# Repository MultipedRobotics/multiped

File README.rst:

.. image:: https://raw.githubusercontent.com/walchko/quadruped/master/pics/spiderbot_dev.JPG
	:target: https://github.com/MomsFriendlyRobotCompany/quadruped
	:width: 75%

Quadruped
============================

.. image:: https://img.shields.io/pypi/v/quadruped.svg
	:target: https://github.com/MomsFriendlyRobotCompany/quadruped
.. image:: https://img.shields.io/pypi/l/quadruped.svg
	:target: https://github.com/MomsFriendlyRobotCompany/quadruped
.. image:: https://travis-ci.org/MomsFriendlyRobotCompany/quadruped.svg?branch=master
	:target: https://travis-ci.org/MomsFriendlyRobotCompany/quadruped

My robot software.

* `YouTube <https://www.youtube.com/watch?v=kH2hlxUfCNg>`_
* `Vimeo <https://player.vimeo.com/video/194676675>`_

Current State
----------------

.. image:: pics/spider.jpg
	:width: 75%

- Processor: Pi Zero W
- Language: python

ToDo:

- design/build boards instead of the jumpers connecting wires
- design the head structure to hold electronics and LCD

Documentation
-------------------

Install
-----------

pip
~~~~~

The recommended way to install this library is::

	pip install quadruped

Development
~~~~~~~~~~~~~

If you wish to develop and submit git-pulls, you can do::

	git clone https://github.com/MomsFriendlyRobotCompany/quadruped
	cd quadruped
	pip install -e .

Testing
~~~~~~~~~

Since I have both python2 and python3 installed, I need to test with both::

	python2 -m nose *.py
	python3 -m nose *.py

Layout
------------

Here is *sort* of the layout of the code:

- Robot(data)
  - Takes a dict of setup values: {'serialPort': /dev/something, 'write': 'bulk'}
		- Engine
		- Gait
- Gait:
	- Gait calculates the foot positions for 1 cycle of a movement
	- command() - plans all feet through 1 gait cycle (12 steps)
	- eachLeg(x,y,z)

- Engine:
	- Engine takes the output from Gait and calculates the servo joint positions
	  for each time stop and each leg in the cycle. It then sends the command to
	  move the servos at the end of the time step.
	- legs[4]
		- servos[3]
			- angle
			- setServoLimits()
			- bulkWrite()
			- syncWrite()
		- coxa, femur, tibia
		- fk() - forward kinematics
		- ik() - inverse kinematics
		- moveFoot(x,y,z) - for inverse kinematics
		- moveFootAngle(a,b,c) - for forward kinematics

The example quadruped (in the examples folder), takes a dictionary. Currently
it takes::

	data = {
		'serialPort': '/dev/tty.usbserial-AL034G2K',
		'write': 'bulk'
	}

If you don't pass it a serial port, then it falls back to a simulated serial
port which does nothing but is useful for testing.

Bulk Writing
--------------

Normally, you would send an individual command to each servo and get a response
back from it. That creates a lot of back an forth communications. Instead,
this uses a bulk write to send commands to all 12 servos at once with no reply.
This results in smoother motion and greatly reduced data transmission.

Building and Documentation
----------------------------

Details for how to build the robot and other information are in the ``docs`` folder
in the `git repo <https://github.com/MomsFriendlyRobotCompany/quadruped/tree/master/docs>`_

Tools
---------

This directory contains several tools for the robot:

- get_leg_angles.py: prints out the joint angles for all 4 legs

.. code-block:: bash

	$ ./get_leg_angles.py /dev/tty.usbserial-AL034G2K
	Opened /dev/tty.usbserial-AL034G2K @ 1000000

	Servos: 1 - 12
	All angles are in degrees
	         Leg 1 |         Leg 2 |         Leg 3 |         Leg 4 |
	   ID | Angle  |   ID | Angle  |   ID | Angle  |   ID | Angle  |
	-----------------------------------------------------------------
	    1 | 149.56 |    4 | 149.56 |    7 | 149.56 |   10 | 149.56
	    2 | 239.88 |    5 | 271.55 |    8 | 269.79 |   11 | 270.38
	    3 |  99.41 |    6 | 100.29 |    9 | 100.00 |   12 |  99.41
	-----------------------------------------------------------------

- get_leg_info.py: prints out servo information for all 12 servos on the robot

.. code-block:: bash

	$ ./get_leg_info.py /dev/tty.usbserial-AL034G2K
	Opened /dev/tty.usbserial-AL034G2K @ 1000000

	Servos: 1 - 12
	--------------------------------------------------
	Servo: 1  		HW Error: 0
	Position [deg]: 149.6  Load:   0.0% CCW
	Voltage [V]  7.0     Temperature [F]:  80.6
	--------------------------------------------------
	Servo: 2  		HW Error: 0
	Position [deg]: 239.6  Load:   0.0% CCW
	Voltage [V]  7.2     Temperature [F]:  80.6
	--------------------------------------------------
	Servo: 3  		HW Error: 0
	Position [deg]:  99.4  Load:   0.0% CCW
	Voltage [V]  7.2     Temperature [F]:  82.4
	--------------------------------------------------
	Servo: 4  		HW Error: 0
	Position [deg]: 149.6  Load:   0.0% CCW
	Voltage [V]  7.3     Temperature [F]:  80.6
	--------------------------------------------------
	Servo: 5  		HW Error: 0
	Position [deg]: 271.6  Load:   0.0% CCW
	Voltage [V]  7.2     Temperature [F]:  80.6
	--------------------------------------------------
	Servo: 6  		HW Error: 0
	Position [deg]: 100.3  Load:   0.0% CCW
	Voltage [V]  7.4     Temperature [F]:  82.4
	--------------------------------------------------
	Servo: 7  		HW Error: 0
	Position [deg]: 149.6  Load:   0.0% CCW
	Voltage [V]  7.2     Temperature [F]:  80.6
	--------------------------------------------------
	Servo: 8  		HW Error: 0
	Position [deg]: 269.8  Load:   0.0% CCW
	Voltage [V]  7.1     Temperature [F]:  78.8
	--------------------------------------------------
	Servo: 9  		HW Error: 0
	Position [deg]:  99.4  Load:   0.8% CCW
	Voltage [V]  7.2     Temperature [F]:  82.4
	--------------------------------------------------
	Servo: 10  		HW Error: 0
	Position [deg]: 149.9  Load:   0.0% CCW
	Voltage [V]  7.1     Temperature [F]:  80.6
	--------------------------------------------------
	Servo: 11  		HW Error: 0
	Position [deg]: 270.1  Load:   0.0% CCW
	Voltage [V]  7.2     Temperature [F]:  80.6
	--------------------------------------------------
	Servo: 12  		HW Error: 0
	Position [deg]:  99.4  Load:   0.0% CCW
	Voltage [V]  7.1     Temperature [F]:  84.2
	--------------------------------------------------

Change Log
-------------

============ ======= ============================
2017-12-25   0.5.0   Clean up and reorg, removed unnecessary libraries
2017-06-07   0.4.1   broke out into package and published to PyPi
2016-08-10   0.0.1   init
============ ======= ============================

MIT License
---------------

**Copyright (c) 2016 Kevin J. Walchko**

Permission is hereby granted, free of charge, to any person obtaining a copy of
this software and associated documentation files (the "Software"), to deal in
the Software without restriction, including without limitation the rights to
use, copy, modify, merge, publish, distribute, sublicense, and/or sell copies
of the Software, and to permit persons to whom the Software is furnished to do
so, subject to the following conditions:

The above copyright notice and this permission notice shall be included in all
copies or substantial portions of the Software.

THE SOFTWARE IS PROVIDED "AS IS", WITHOUT WARRANTY OF ANY KIND, EXPRESS OR
IMPLIED, INCLUDING BUT NOT LIMITED TO THE WARRANTIES OF MERCHANTABILITY, FITNESS
FOR A PARTICULAR PURPOSE AND NONINFRINGEMENT. IN NO EVENT SHALL THE AUTHORS OR
COPYRIGHT HOLDERS BE LIABLE FOR ANY CLAIM, DAMAGES OR OTHER LIABILITY, WHETHER
IN AN ACTION OF CONTRACT, TORT OR OTHERWISE, ARISING FROM, OUT OF OR IN
CONNECTION WITH THE SOFTWARE OR THE USE OR OTHER DEALINGS IN THE SOFTWARE.

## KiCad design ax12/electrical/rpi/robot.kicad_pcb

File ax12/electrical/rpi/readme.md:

# RPi Adaptor Board

This ties the RPi to sensors and actuators.

## Schematic

[pdf schematic](rpi.pdf)

## Board

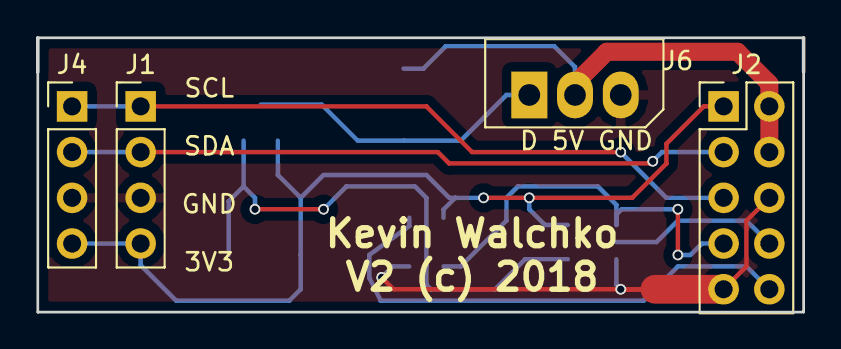
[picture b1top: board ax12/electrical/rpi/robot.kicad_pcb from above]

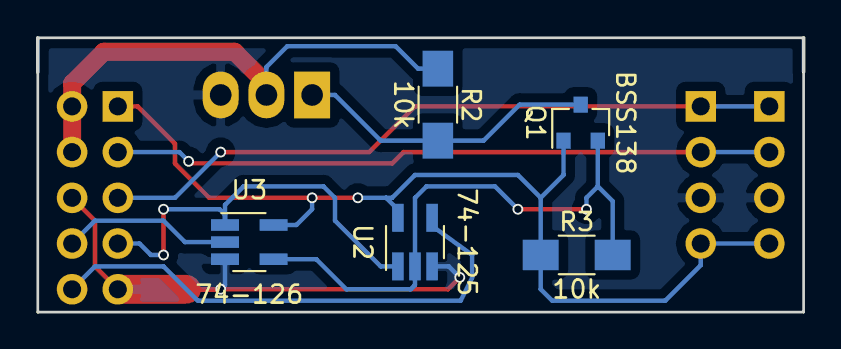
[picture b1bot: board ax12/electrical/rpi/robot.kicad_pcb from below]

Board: 2 copper layers, 42.5 x 15.2 mm, 9 parts (5 on the bottom side), 10 nets.

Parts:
J1, J4: i2c; Pin_Header_Straight_1x04_Pitch2.54mm
J2: Pi Header; Pin_Header_Straight_2x05_Pitch2.54mm
J6: Power/Data Input; Molex_SPOX-5267_22-03-5035_03x2.54mm_Straight
Q1: BSS138; SOT-23
R2, R3: 10k; R_1206_HandSoldering
U2: 74-125; SOT-23-5_HandSoldering
U3: 74-126; SOT-23-5_HandSoldering

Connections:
+3V3: J1.4, J2.1, J4.4, Q1.1, R3.1, U2.5, U3.5
+5V: J2.2, J2.4, J6.2, R2.1
DATA: J6.1, Q1.3, R2.2
DTR: J2.7, U2.1, U3.1
GND: J1.3, J2.6, J2.9, J4.3, J6.3, U2.3, U3.3
unnamed: Q1.2, R3.2, U2.2, U3.4
RXI: J2.10, U2.4
SCL: J1.1, J2.5, J4.1
SDA: J1.2, J2.3, J4.2
TXO: J2.8, U3.2

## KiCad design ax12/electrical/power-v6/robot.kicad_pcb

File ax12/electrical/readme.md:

# Electrical

## Raspberry Pi

Adaptor board to connect the RPi to sensors/actuators

## Power

Power distribution board

### Pololu 12V Buck Regulator

# Bill of Materials (BoM)

| Part | Qnty | Each | Cost |
|---|---|---|---|
|  |  |  |  |

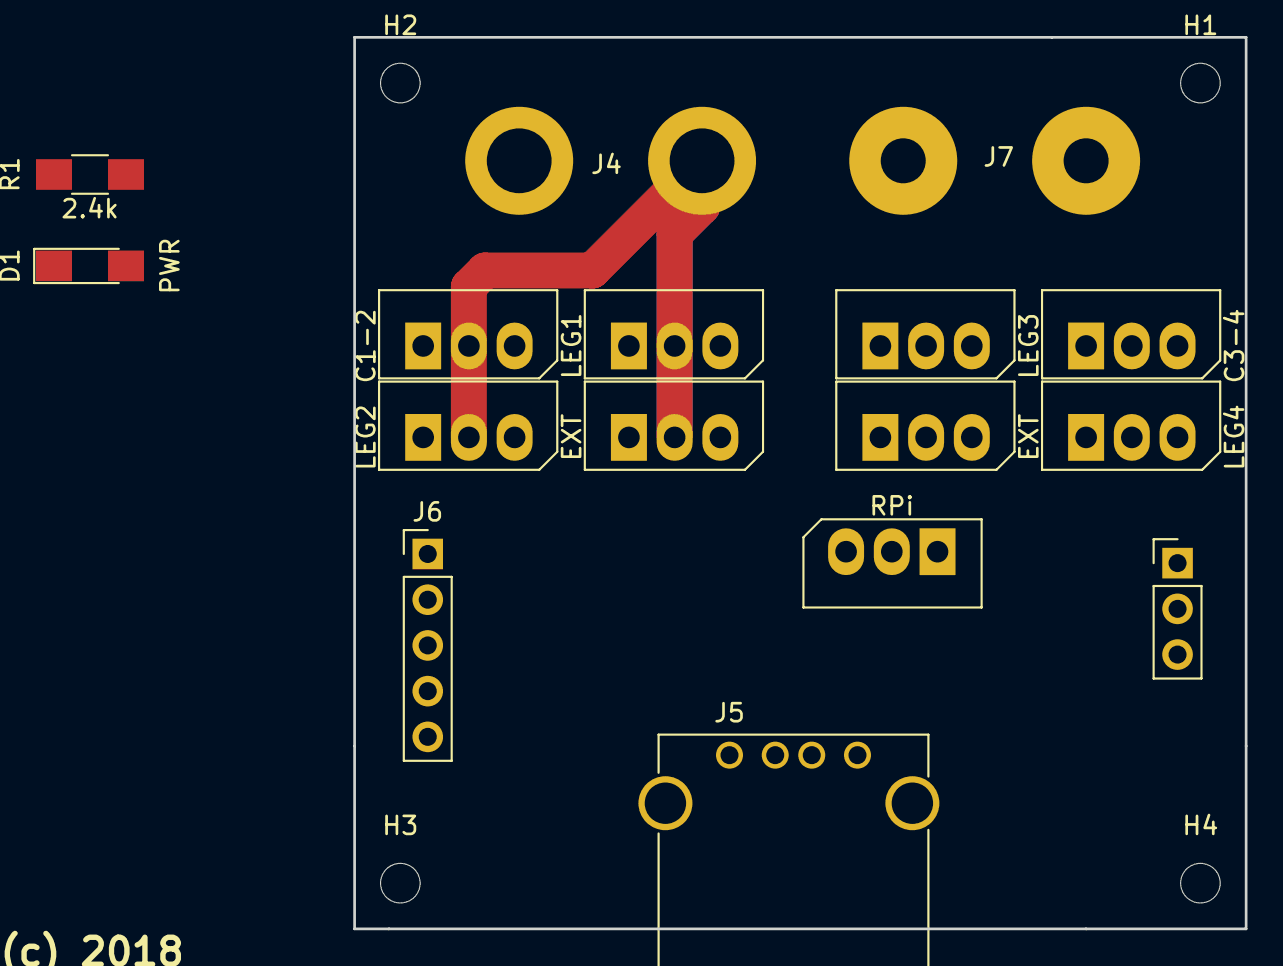
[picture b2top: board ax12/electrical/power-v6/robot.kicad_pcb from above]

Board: 2 copper layers, 49.5 x 49.5 mm, 20 parts (0 on the bottom side), 6 nets.

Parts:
D1: PWR; LED_1206_HandSoldering
H1, H2, H3, H4: MountingHole; MountingHole_2.2mm_M2
J1: C1-2; Molex_SPOX-5267_22-03-5035_03x2.54mm_Straight
J2: RPi; Molex_SPOX-5267_22-03-5035_03x2.54mm_Straight
J3: Data; Pin_Header_Straight_1x03_Pitch2.54mm
J4: Leg1-2; WireConnection_2.50mmDrill_LargePad
J5: USB_A
J6: 5V Pwr; Pin_Header_Straight_1x05_Pitch2.54mm
J7: Leg3-4; WireConnection_2.50mmDrill_LargePad
J8: LEG1; Molex_SPOX-5267_22-03-5035_03x2.54mm_Straight
J10: LEG2; Molex_SPOX-5267_22-03-5035_03x2.54mm_Straight
J11, J13: EXT; Molex_SPOX-5267_22-03-5035_03x2.54mm_Straight
J12: LEG4; Molex_SPOX-5267_22-03-5035_03x2.54mm_Straight
J14: C3-4; Molex_SPOX-5267_22-03-5035_03x2.54mm_Straight
J15: LEG3; Molex_SPOX-5267_22-03-5035_03x2.54mm_Straight
R1: 2.4k; R_1206_HandSoldering

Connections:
+5V: J2.2, J5.1, J6.5
DATA: J1.1, J2.1, J3.1, J8.1, J10.1, J11.1, J12.1, J13.1, J14.1, J15.1
GND: J1.3, J2.3, J3.3, J4.1, J5.4, J5.5, J6.3, J6.4, J7.1, J8.3, J10.3, J11.3, J12.3, J13.3, J14.3, J15.3, R1.2
unnamed: D1.1, R1.1
unnamed: D1.2, J1.2, J4.2, J6.2, J8.2, J10.2, J11.2
unnamed: J3.2, J7.2, J12.2, J13.2, J14.2, J15.2

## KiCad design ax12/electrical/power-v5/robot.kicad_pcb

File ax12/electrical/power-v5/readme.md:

# Power Distribution Board

## Schematic

[pdf schematic](rpi.pdf)

## Board

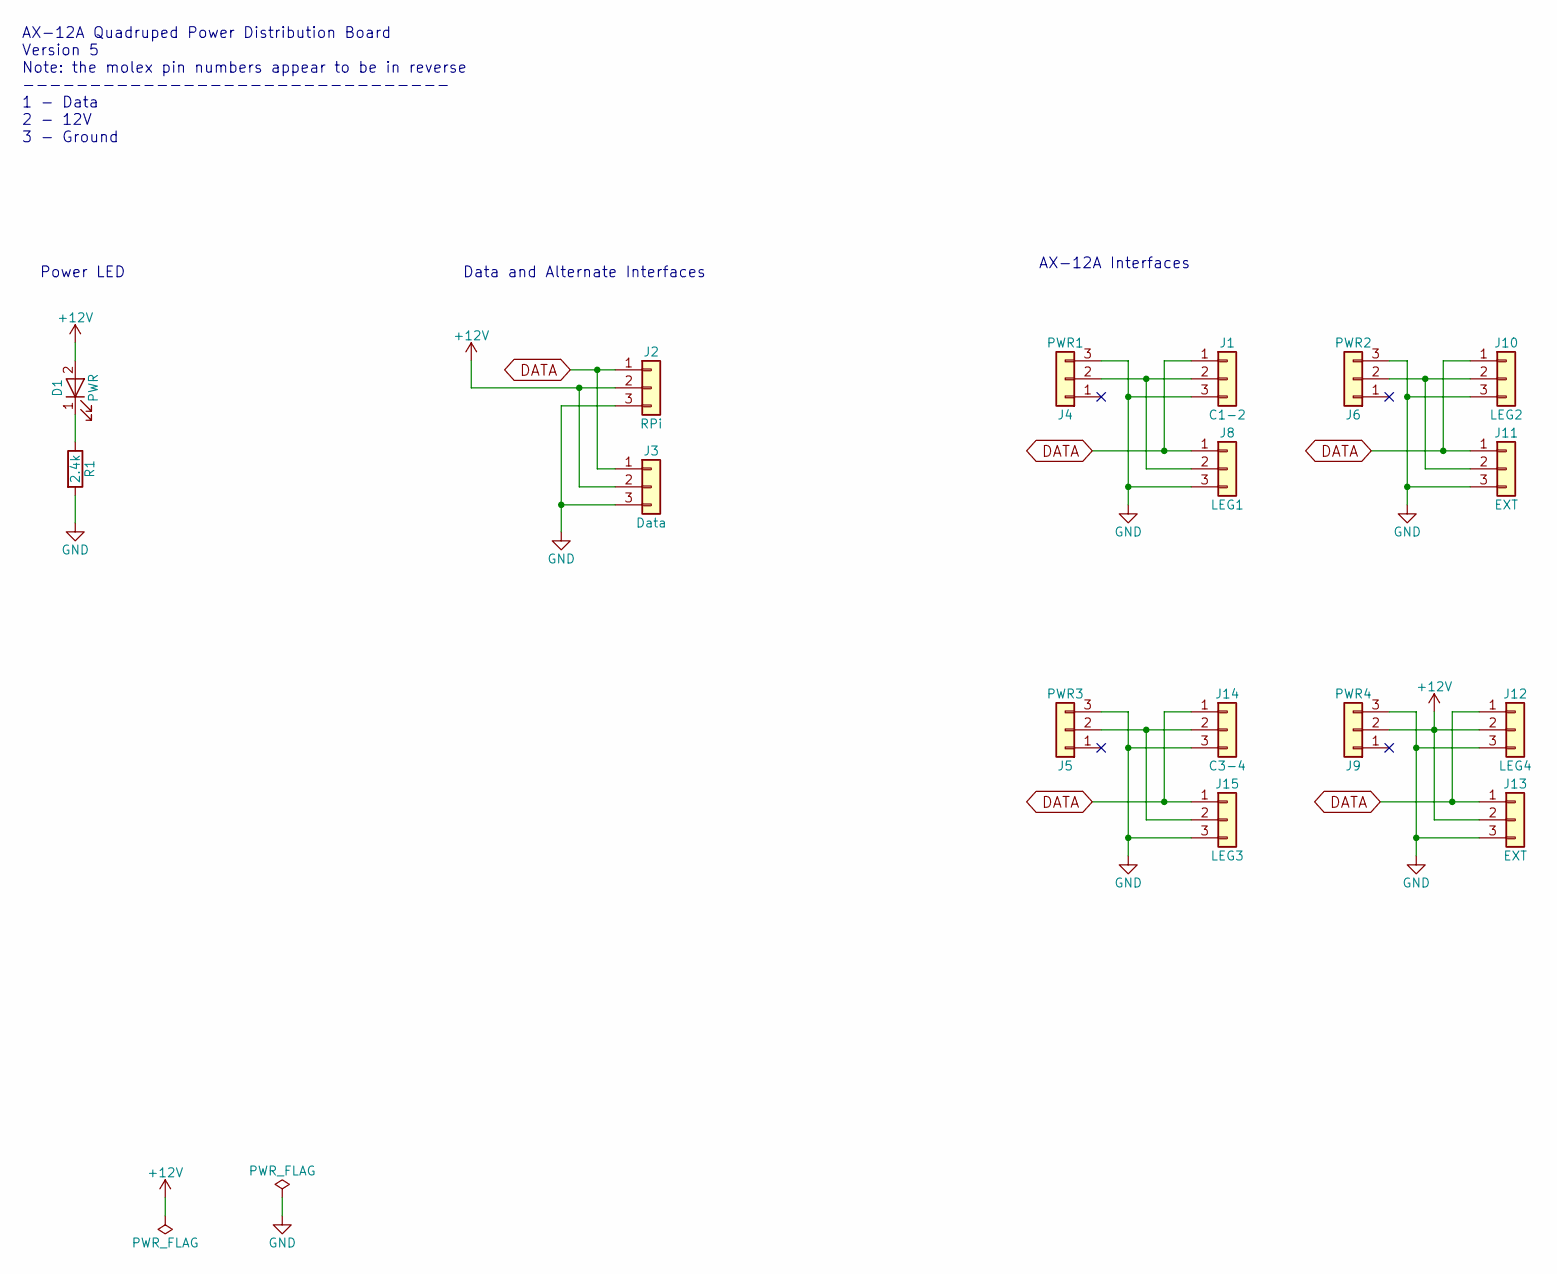
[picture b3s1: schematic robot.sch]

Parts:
D1: PWR; LED_1206_HandSoldering
J1: C1-2; Molex_SPOX-5267_22-03-5035_03x2.54mm_Straight
J2: RPi; Molex_SPOX-5267_22-03-5035_03x2.54mm_Straight
J3: Data; Pin_Header_Straight_1x03_Pitch2.54mm
J4: PWR1; Molex_SPOX-5267_22-03-5035_03x2.54mm_Straight
J5: PWR3; Molex_SPOX-5267_22-03-5035_03x2.54mm_Straight
J6: PWR2; Molex_SPOX-5267_22-03-5035_03x2.54mm_Straight
J8: LEG1; Molex_SPOX-5267_22-03-5035_03x2.54mm_Straight
J9: PWR4; Molex_SPOX-5267_22-03-5035_03x2.54mm_Straight
J10: LEG2; Molex_SPOX-5267_22-03-5035_03x2.54mm_Straight
J11, J13: EXT; Molex_SPOX-5267_22-03-5035_03x2.54mm_Straight
J12: LEG4; Molex_SPOX-5267_22-03-5035_03x2.54mm_Straight
J14: C3-4; Molex_SPOX-5267_22-03-5035_03x2.54mm_Straight
J15: LEG3; Molex_SPOX-5267_22-03-5035_03x2.54mm_Straight
R1: 2.4k; R_1206_HandSoldering

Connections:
+12V: D1.2 (A), J2.2, J3.2, J9.2, J12.2, J13.2
DATA: J1.1, J2.1, J3.1, J8.1, J10.1, J11.1, J12.1, J13.1, J14.1, J15.1
GND: J1.3, J2.3, J3.3, J4.3, J5.3, J6.3, J8.3, J9.3, J10.3, J11.3, J12.3, J13.3, J14.3, J15.3, R1.2
unnamed: D1.1 (K), R1.1
unnamed: J1.2, J4.2, J8.2
unnamed: J6.2, J10.2, J11.2
unnamed: J5.2, J14.2, J15.2

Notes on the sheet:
AX-12A Quadruped Power Distribution Board Version 5 Note: the molex pin numbers appear to be in reverse -------------------------------- 1 - Data 2 - 12V 3 - Ground
Power LED
AX-12A Interfaces
Data and Alternate Interfaces

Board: 2 copper layers, 16 parts (0 on the bottom side), 7 nets, no tracks yet.

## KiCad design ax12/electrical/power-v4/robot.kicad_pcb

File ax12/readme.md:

# AX-12A Quadruped

Nature loves animals/insects with legs. Even birds have legs! Legs allow for easier
navigation across rough terrain. The more legs you have, the more redundant and
robust you are. If you are a centipede and you break a few legs, no big deal.
However, if you are a human and break one leg, then walking (forget running)
becomes extremely difficult.

In robotics you see many different types of walking robots. Common ones are:
2 legs, four legs, and 6 legs. There are advantages and disadvantages for each
of these types of robots.

- 2 legs
    - balancing and shifting the body's center of mass is critical to the
robot not falling over
    - the 2 legs are generally need to be more powerful to lift the body mass
- 4 legs:
    - there is an inherent stability with this configuration. You only need 3
    legs (tripod) to keep the robot standing, leaving one leg to move freely
    as needed
    - each of the legs can be weaker (which also translates into cost $$$) than
    its 2 legged counter part, but you still have more of them, so it is probably
    still more expensive
    - However, there is still a lot of motors, data lines, coordination complexity
    than if you only had 2 legs
- 6 legs:
    - having more than 4 legs contains all of the same advantages/disadvantages
    of 4 legs
    - you also have more redundancy, essentially able to loose 2 legs and keep
    walking
    - there are also more types of gaits available to you, which is a fancy word
    for how you control your leg moves when walking, trotting, running, etc

**Still under development**

- [Mechanical Hardware](mechanical/)
- [Electrical Hardware](electrical/)

MIT License
-----------

**Copyright (c) 2018 Kevin J. Walchko**

Permission is hereby granted, free of charge, to any person obtaining a
copy of this software and associated documentation files (the
"Software"), to deal in the Software without restriction, including
without limitation the rights to use, copy, modify, merge, publish,
distribute, sublicense, and/or sell copies of the Software, and to
permit persons to whom the Software is furnished to do so, subject to
the following conditions:

The above copyright notice and this permission notice shall be included
in all copies or substantial portions of the Software.

THE SOFTWARE IS PROVIDED "AS IS", WITHOUT WARRANTY OF ANY KIND,
EXPRESS OR IMPLIED, INCLUDING BUT NOT LIMITED TO THE WARRANTIES OF
MERCHANTABILITY, FITNESS FOR A PARTICULAR PURPOSE AND NONINFRINGEMENT.
IN NO EVENT SHALL THE AUTHORS OR COPYRIGHT HOLDERS BE LIABLE FOR ANY
CLAIM, DAMAGES OR OTHER LIABILITY, WHETHER IN AN ACTION OF CONTRACT,
TORT OR OTHERWISE, ARISING FROM, OUT OF OR IN CONNECTION WITH THE
SOFTWARE OR THE USE OR OTHER DEALINGS IN THE SOFTWARE.

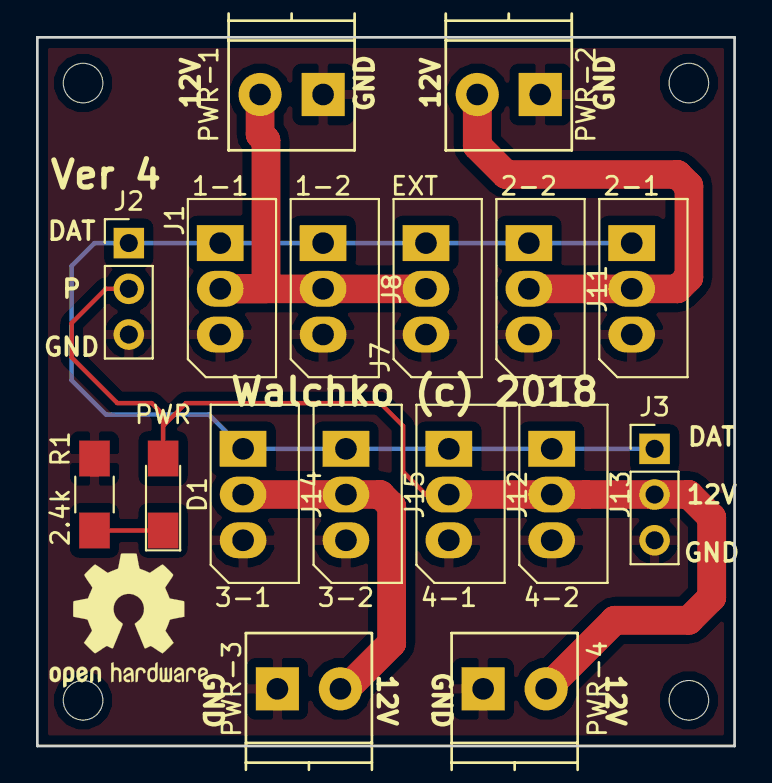
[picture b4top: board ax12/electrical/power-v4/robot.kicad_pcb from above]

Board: 2 copper layers, 38.7 x 39.4 mm, 17 parts (0 on the bottom side), 7 nets.

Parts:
D1: PWR; LED_1206_HandSoldering
J1: 1-1; Molex_SPOX-5267_22-03-5035_03x2.54mm_Straight
J2, J3: Data; Pin_Header_Straight_1x03_Pitch2.54mm
J4: PWR-4; TerminalBlock_Phoenix_PT-3.5mm_2pol
J5: PWR-3; TerminalBlock_Phoenix_PT-3.5mm_2pol
J6: PWR-1; TerminalBlock_Phoenix_PT-3.5mm_2pol
J7: EXT; Molex_SPOX-5267_22-03-5035_03x2.54mm_Straight
J8: 1-2; Molex_SPOX-5267_22-03-5035_03x2.54mm_Straight
J9: PWR-2; TerminalBlock_Phoenix_PT-3.5mm_2pol
J10: 2-1; Molex_SPOX-5267_22-03-5035_03x2.54mm_Straight
J11: 2-2; Molex_SPOX-5267_22-03-5035_03x2.54mm_Straight
J12: 4-1; Molex_SPOX-5267_22-03-5035_03x2.54mm_Straight
J13: 4-2; Molex_SPOX-5267_22-03-5035_03x2.54mm_Straight
J14: 3-1; Molex_SPOX-5267_22-03-5035_03x2.54mm_Straight
J15: 3-2; Molex_SPOX-5267_22-03-5035_03x2.54mm_Straight
R1: 2.4k; R_1206_HandSoldering

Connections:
+12V: D1.2, J2.2, J3.2, J4.2, J12.2, J13.2
DATA: J1.1, J2.1, J3.1, J7.1, J8.1, J10.1, J11.1, J12.1, J13.1, J14.1, J15.1
GND: J1.3, J2.3, J3.3, J4.1, J5.1, J6.1, J7.3, J8.3, J9.1, J10.3, J11.3, J12.3, J13.3, J14.3, J15.3, R1.2
unnamed: D1.1, R1.1
unnamed: J1.2, J6.2, J7.2, J8.2
unnamed: J9.2, J10.2, J11.2
unnamed: J5.2, J14.2, J15.2

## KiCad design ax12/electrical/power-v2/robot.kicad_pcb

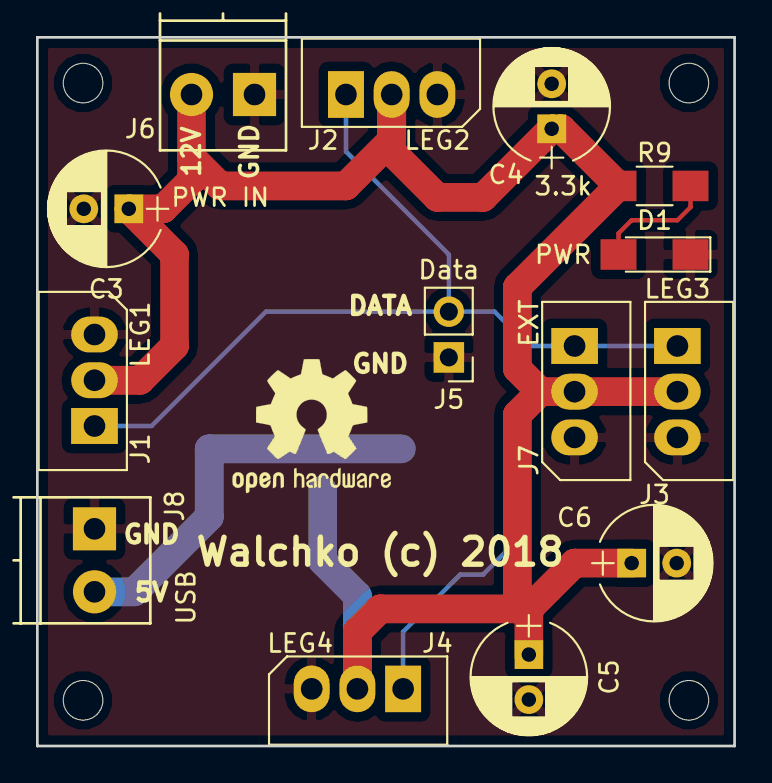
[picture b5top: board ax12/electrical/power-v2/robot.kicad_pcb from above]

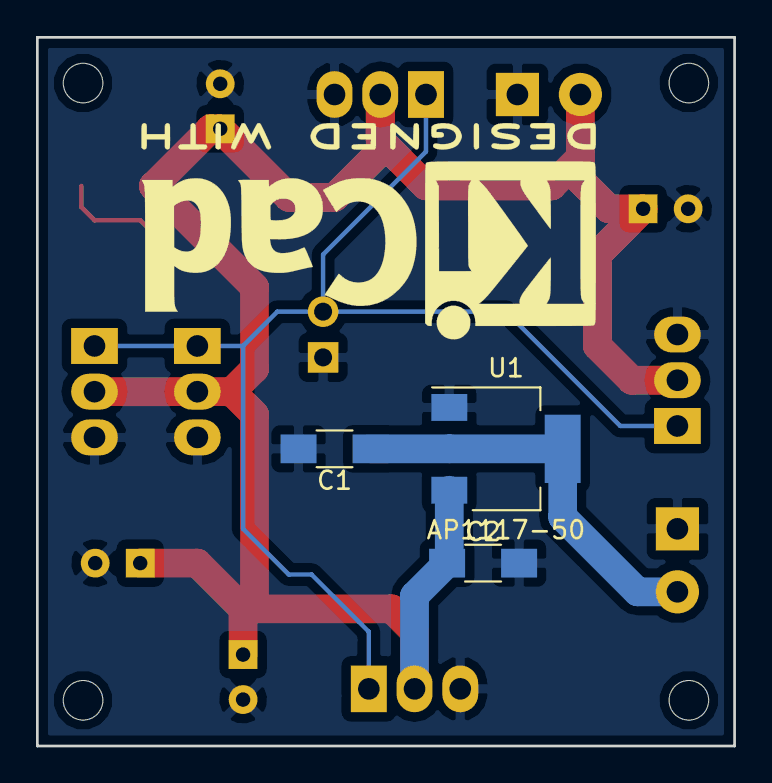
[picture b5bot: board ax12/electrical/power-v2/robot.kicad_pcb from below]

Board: 2 copper layers, 38.7 x 39.4 mm, 17 parts (3 on the bottom side), 5 nets.

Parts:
C1, C2: C; C_1206_HandSoldering
C3, C4, C5, C6: .1; CP_Radial_D6.3mm_P2.50mm
D1: PWR; LED_1206_HandSoldering
J1: LEG1; Molex_SPOX-5267_22-03-5035_03x2.54mm_Straight
J2: LEG2; Molex_SPOX-5267_22-03-5035_03x2.54mm_Straight
J3: LEG3; Molex_SPOX-5267_22-03-5035_03x2.54mm_Straight
J4: LEG4; Molex_SPOX-5267_22-03-5035_03x2.54mm_Straight
J5: Data; Pin_Header_Straight_1x02_Pitch2.54mm
J6: PWR IN; TerminalBlock_Phoenix_PT-3.5mm_2pol
J7: EXT; Molex_SPOX-5267_22-03-5035_03x2.54mm_Straight
J8: USB; TerminalBlock_Phoenix_PT-3.5mm_2pol
R9: 3.3k; R_1206_HandSoldering
U1: AP1117-50; SOT-223-3_TabPin2

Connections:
+5V: C1.1, J8.2, U1.2
+12V: C2.1, C3.1, C4.1, C5.1, C6.1, J1.2, J2.2, J3.2, J4.2, J6.2, J7.2, R9.1, U1.3
DATA: J1.1, J2.1, J3.1, J4.1, J5.2, J7.1
GND: C1.2, C2.2, C3.2, C4.2, C5.2, C6.2, D1.1, J1.3, J2.3, J3.3, J4.3, J5.1, J6.1, J7.3, J8.1, U1.1
unnamed: D1.2, R9.2

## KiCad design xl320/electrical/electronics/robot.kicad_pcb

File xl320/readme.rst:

.. image:: https://raw.githubusercontent.com/walchko/quadruped/master/pics/spiderbot_dev.JPG
	:target: https://github.com/MomsFriendlyRobotCompany/quadruped
	:width: 75%

XL-320 Quadruped
============================

My robot software.

* `YouTube <https://www.youtube.com/watch?v=kH2hlxUfCNg>`_
* `Vimeo <https://player.vimeo.com/video/194676675>`_

Documentation
-------------------

Install
-----------

pip
~~~~~

The recommended way to install this library is::

	pip install quadruped

Development
~~~~~~~~~~~~~

If you wish to develop and submit git-pulls, you can do::

	git clone https://github.com/MomsFriendlyRobotCompany/quadruped
	cd quadruped
	pip install -e .

Testing
~~~~~~~~~

Since I have both python2 and python3 installed, I need to test with both::

	python2 -m nose *.py
	python3 -m nose *.py

Layout
------------

Here is *sort* of the layout of the code:

- Robot(data)
  - Takes a dict of setup values: {'serialPort': /dev/something, 'write': 'bulk'}
		- Engine
		- Gait
- Gait:
	- Gait calculates the foot positions for 1 cycle of a movement
	- command() - plans all feet through 1 gait cycle (12 steps)
	- eachLeg(x,y,z)

- Engine:
	- Engine takes the output from Gait and calculates the servo joint positions
	  for each time stop and each leg in the cycle. It then sends the command to
	  move the servos at the end of the time step.
	- legs[4]
		- servos[3]
			- angle
			- setServoLimits()
			- bulkWrite()
			- syncWrite()
		- coxa, femur, tibia
		- fk() - forward kinematics
		- ik() - inverse kinematics
		- moveFoot(x,y,z) - for inverse kinematics
		- moveFootAngle(a,b,c) - for forward kinematics

The example quadruped (in the examples folder), takes a dictionary. Currently
it takes::

	data = {
		'serialPort': '/dev/tty.usbserial-AL034G2K',
		'write': 'bulk'
	}

If you don't pass it a serial port, then it falls back to a simulated serial
port which does nothing but is useful for testing.

Tools
---------

This directory contains several tools for the robot:

- get_leg_angles.py: prints out the joint angles for all 4 legs

.. code-block:: bash

	$ ./get_leg_angles.py /dev/tty.usbserial-AL034G2K
	Opened /dev/tty.usbserial-AL034G2K @ 1000000

	Servos: 1 - 12
	All angles are in degrees
	         Leg 1 |         Leg 2 |         Leg 3 |         Leg 4 |
	   ID | Angle  |   ID | Angle  |   ID | Angle  |   ID | Angle  |
	-----------------------------------------------------------------
	    1 | 149.56 |    4 | 149.56 |    7 | 149.56 |   10 | 149.56
	    2 | 239.88 |    5 | 271.55 |    8 | 269.79 |   11 | 270.38
	    3 |  99.41 |    6 | 100.29 |    9 | 100.00 |   12 |  99.41
	-----------------------------------------------------------------

- get_leg_info.py: prints out servo information for all 12 servos on the robot

.. code-block:: bash

	$ ./get_leg_info.py /dev/tty.usbserial-AL034G2K
	Opened /dev/tty.usbserial-AL034G2K @ 1000000

	Servos: 1 - 12
	--------------------------------------------------
	Servo: 1  		HW Error: 0
	Position [deg]: 149.6  Load:   0.0% CCW
	Voltage [V]  7.0     Temperature [F]:  80.6
	--------------------------------------------------
	Servo: 2  		HW Error: 0
	Position [deg]: 239.6  Load:   0.0% CCW
	Voltage [V]  7.2     Temperature [F]:  80.6
	--------------------------------------------------
	Servo: 3  		HW Error: 0
	Position [deg]:  99.4  Load:   0.0% CCW
	Voltage [V]  7.2     Temperature [F]:  82.4
	--------------------------------------------------
	Servo: 4  		HW Error: 0
	Position [deg]: 149.6  Load:   0.0% CCW
	Voltage [V]  7.3     Temperature [F]:  80.6
	--------------------------------------------------
	Servo: 5  		HW Error: 0
	Position [deg]: 271.6  Load:   0.0% CCW
	Voltage [V]  7.2     Temperature [F]:  80.6
	--------------------------------------------------
	Servo: 6  		HW Error: 0
	Position [deg]: 100.3  Load:   0.0% CCW
	Voltage [V]  7.4     Temperature [F]:  82.4
	--------------------------------------------------
	Servo: 7  		HW Error: 0
	Position [deg]: 149.6  Load:   0.0% CCW
	Voltage [V]  7.2     Temperature [F]:  80.6
	--------------------------------------------------
	Servo: 8  		HW Error: 0
	Position [deg]: 269.8  Load:   0.0% CCW
	Voltage [V]  7.1     Temperature [F]:  78.8
	--------------------------------------------------
	Servo: 9  		HW Error: 0
	Position [deg]:  99.4  Load:   0.8% CCW
	Voltage [V]  7.2     Temperature [F]:  82.4
	--------------------------------------------------
	Servo: 10  		HW Error: 0
	Position [deg]: 149.9  Load:   0.0% CCW
	Voltage [V]  7.1     Temperature [F]:  80.6
	--------------------------------------------------
	Servo: 11  		HW Error: 0
	Position [deg]: 270.1  Load:   0.0% CCW
	Voltage [V]  7.2     Temperature [F]:  80.6
	--------------------------------------------------
	Servo: 12  		HW Error: 0
	Position [deg]:  99.4  Load:   0.0% CCW
	Voltage [V]  7.1     Temperature [F]:  84.2
	--------------------------------------------------

Change Log
-------------

============ ======= ============================
2018-02-05   0.8.0   Code now supports both XL-320 and AX-12A servos
2017-12-25   0.5.0   Clean up and reorg, removed unnecessary libraries
2017-06-07   0.4.1   broke out into package and published to PyPi
2016-08-10   0.0.1   init
============ ======= ============================

MIT License
---------------

**Copyright (c) 2016 Kevin J. Walchko**

Permission is hereby granted, free of charge, to any person obtaining a copy of
this software and associated documentation files (the "Software"), to deal in
the Software without restriction, including without limitation the rights to
use, copy, modify, merge, publish, distribute, sublicense, and/or sell copies
of the Software, and to permit persons to whom the Software is furnished to do
so, subject to the following conditions:

The above copyright notice and this permission notice shall be included in all
copies or substantial portions of the Software.

THE SOFTWARE IS PROVIDED "AS IS", WITHOUT WARRANTY OF ANY KIND, EXPRESS OR
IMPLIED, INCLUDING BUT NOT LIMITED TO THE WARRANTIES OF MERCHANTABILITY, FITNESS
FOR A PARTICULAR PURPOSE AND NONINFRINGEMENT. IN NO EVENT SHALL THE AUTHORS OR
COPYRIGHT HOLDERS BE LIABLE FOR ANY CLAIM, DAMAGES OR OTHER LIABILITY, WHETHER
IN AN ACTION OF CONTRACT, TORT OR OTHERWISE, ARISING FROM, OUT OF OR IN
CONNECTION WITH THE SOFTWARE OR THE USE OR OTHER DEALINGS IN THE SOFTWARE.

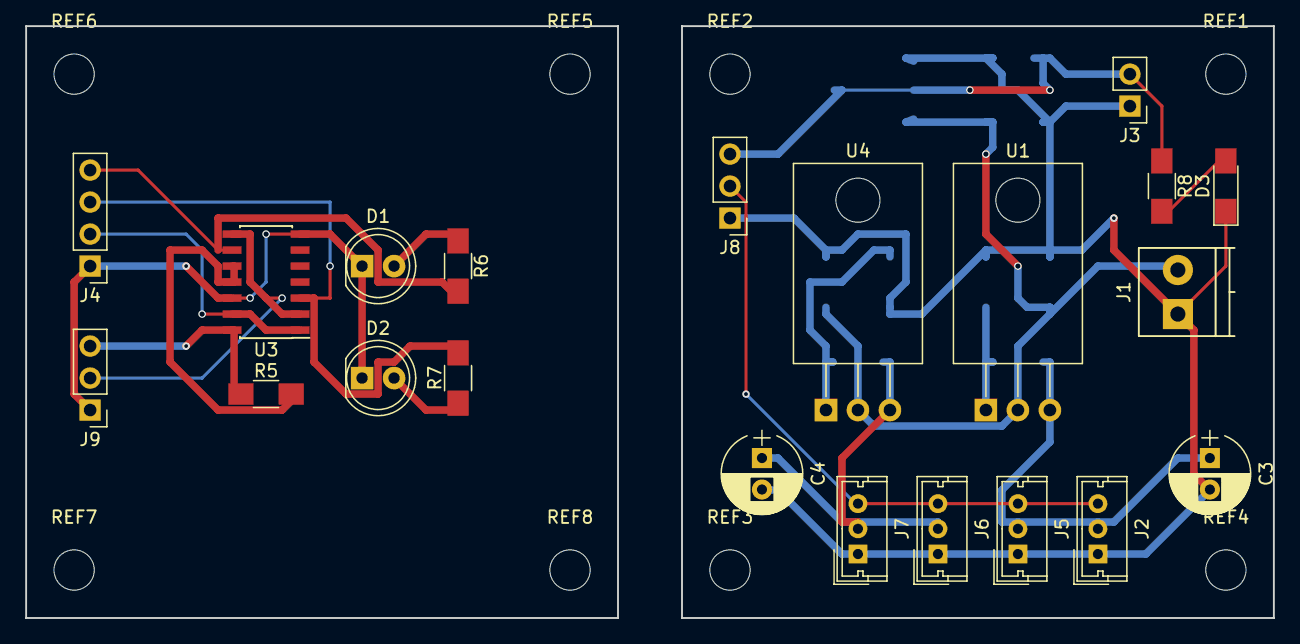
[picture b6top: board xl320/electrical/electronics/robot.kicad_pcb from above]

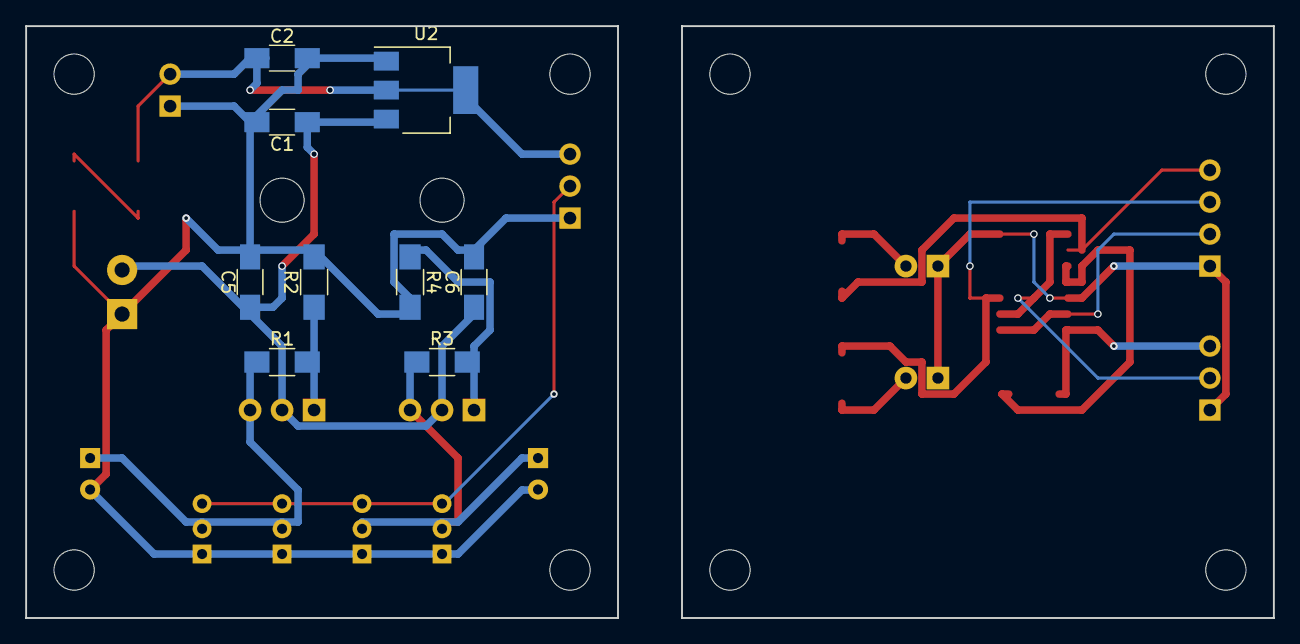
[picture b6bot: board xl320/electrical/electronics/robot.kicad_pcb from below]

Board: 2 copper layers, 99.1 x 47.0 mm, 38 parts (9 on the bottom side), 18 nets.

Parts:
C1, C2, C5, C6: C; C_1206_HandSoldering
C3, C4: .1; CP_Radial_D6.3mm_P2.50mm
D1: TX; LED_D5.0mm
D2: RX; LED_D5.0mm
D3: PWR; LED_1206_HandSoldering
J1: 12V; TerminalBlock_Phoenix_PT-3.5mm_2pol
J2: LEG1; Molex_MicroLatch-53253-0370_03x2.00mm_Straight
J3: Pi USB Pwr; Pin_Header_Straight_1x02_Pitch2.54mm
J4: Serial; Pin_Header_Straight_1x04_Pitch2.54mm
J5: LEG2; Molex_MicroLatch-53253-0370_03x2.00mm_Straight
J6: LEG3; Molex_MicroLatch-53253-0370_03x2.00mm_Straight
J7: LEG4; Molex_MicroLatch-53253-0370_03x2.00mm_Straight
J8: Data P; Pin_Header_Straight_1x03_Pitch2.54mm
J9: Data S; Pin_Header_Straight_1x03_Pitch2.54mm
R1, R3, R6, R7, R8: 330; R_1206_HandSoldering
R2, R4: 1.8k; R_1206_HandSoldering
R5: 10k; R_1206_HandSoldering
REF1, REF2, REF3, REF5, REF6, REF7, REF8: MountingHole_3.2mm_M3
REF4: 3.2mm_M3; MountingHole_3.2mm_M3
U1: LM317_12; TO-220-3_Horizontal
U2: AP1117-50; SOT-223-3_TabPin2
U3: 74LS126; SOIC-14_3.9x8.7mm_Pitch1.27mm
U4: LM317_34; TO-220-3_Horizontal

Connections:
+5V: C2.1, J3.2, J8.3, R8.1, U2.2
+5VA: J9.3, R5.1, U3.14
+12V: C1.1, C5.1, C6.1, J1.2, U1.2, U2.3, U4.2
/DATA: J2.3, J5.3, J6.3, J7.3, J8.2
/DTR: J4.2, U3.1, U3.13
/PWR12: C3.1, J2.2, J5.2, R1.1, U1.3
/PWR34: C4.1, J6.2, J7.2, R3.1, U4.3
/RXO: J4.3, R7.2, U3.3
/TXI: J4.4, R6.2, U3.9
GND: D1.1, D2.1, J4.1, J9.1, U3.7, U3.12
GNDA: C1.2, C2.2, C3.2, C4.2, C5.2, C6.2, D3.1, J1.1, J2.1, J3.1, J5.1, J6.1, J7.1, J8.1, R2.2, R4.2, U2.1
unnamed: D1.2, R6.1
unnamed: D2.2, R7.1
unnamed: D3.2, R8.2
unnamed: J9.2, U3.2, U3.8
unnamed: R1.2, R2.1, U1.1
unnamed: R3.2, R4.1, U4.1
unnamed: R5.2, U3.10, U3.11

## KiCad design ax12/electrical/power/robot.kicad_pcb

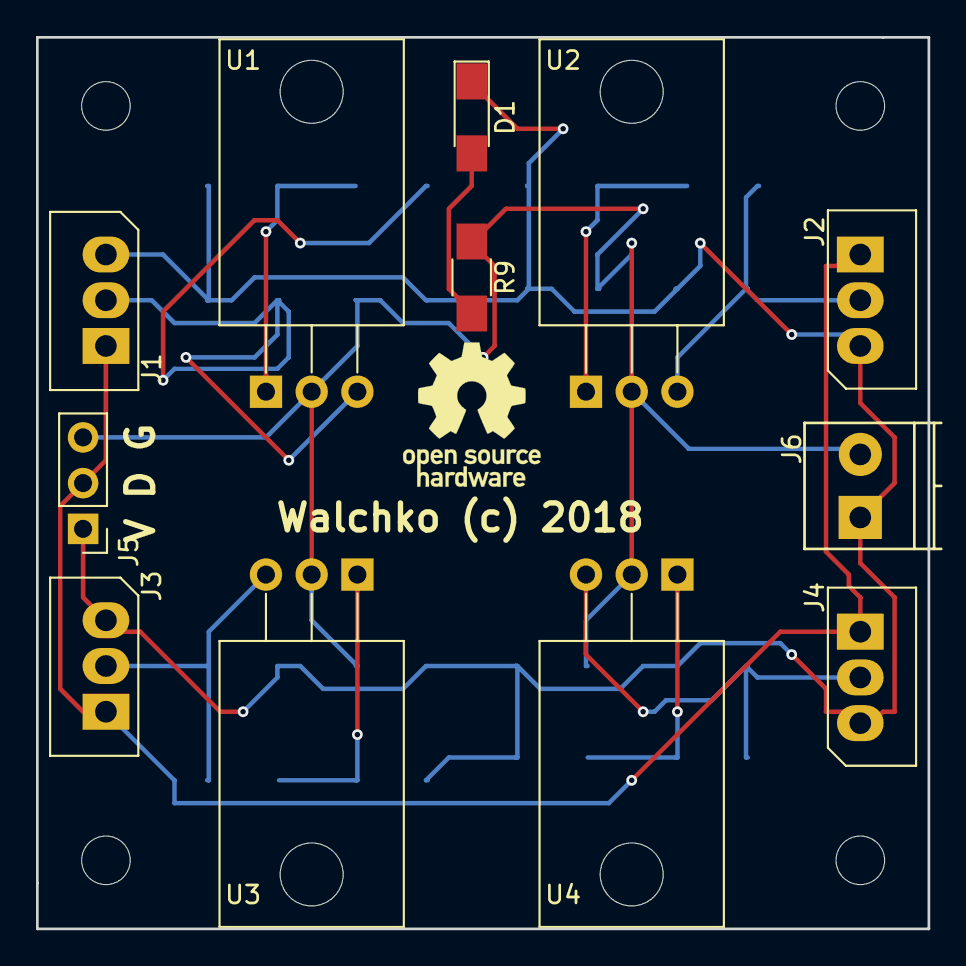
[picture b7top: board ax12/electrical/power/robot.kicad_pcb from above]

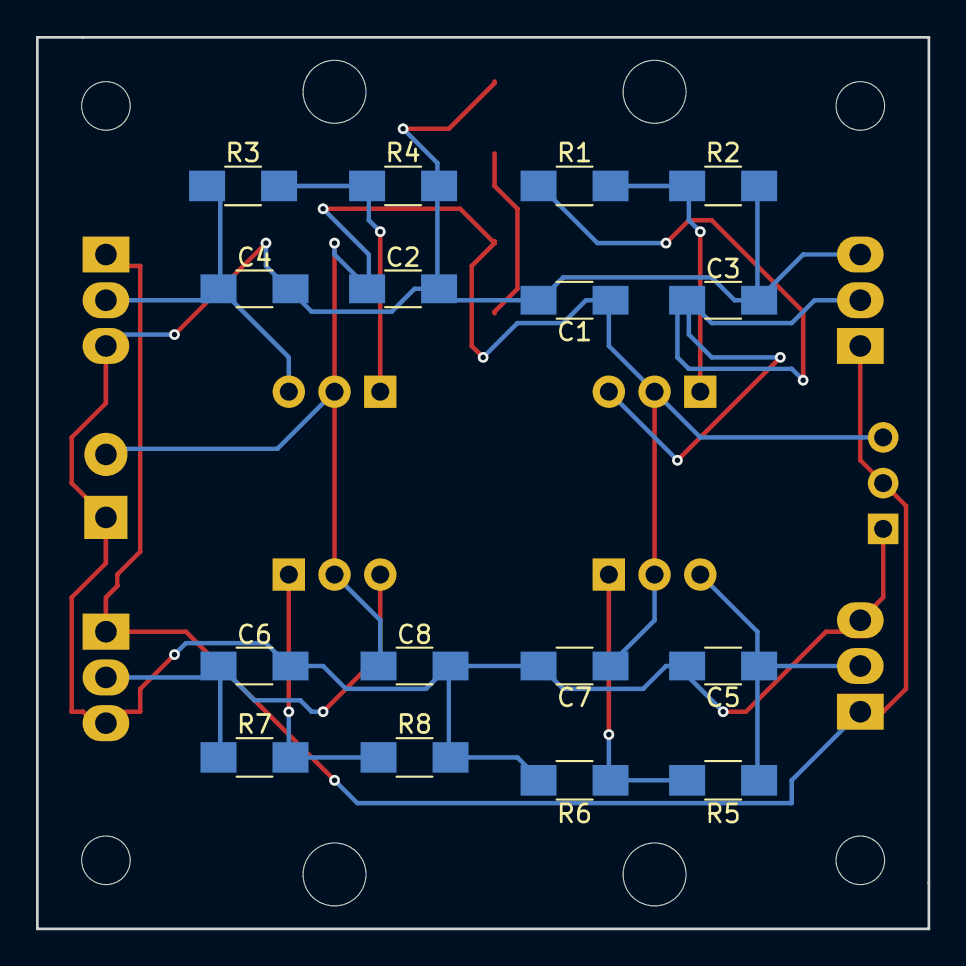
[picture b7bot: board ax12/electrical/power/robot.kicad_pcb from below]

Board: 2 copper layers, 49.5 x 49.5 mm, 28 parts (16 on the bottom side), 12 nets.

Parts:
C1, C2, C7, C8: C; C_1206_HandSoldering
C3, C4, C5, C6: .1; C_1206_HandSoldering
D1: PWR; LED_1206_HandSoldering
J1: LEG1; Molex_SPOX-5267_22-03-5035_03x2.54mm_Straight
J2: LEG2; Molex_SPOX-5267_22-03-5035_03x2.54mm_Straight
J3: LEG4; Molex_SPOX-5267_22-03-5035_03x2.54mm_Straight
J4: LEG3; Molex_SPOX-5267_22-03-5035_03x2.54mm_Straight
J5: Data P; Pin_Header_Straight_1x03_Pitch2.54mm
J6: PWR IN; TerminalBlock_Phoenix_PT-3.5mm_2pol
R1, R3, R5, R7: 390; R_1206_HandSoldering
R2, R4, R6, R8: 3.3k; R_1206_HandSoldering
R9: 330; R_1206_HandSoldering
U1, U2: LM317_12; TO-220-3_Horizontal
U3, U4: LM317_34; TO-220-3_Horizontal

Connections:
+VDC: C1.1, C2.1, C7.1, C8.1, J5.3, J6.2, R9.1, U1.2, U2.2, U3.2, U4.2
DATA: J1.1, J2.1, J3.1, J4.1, J5.2
GNDA: C1.2, C2.2, C3.2, C4.2, C5.2, C6.2, C7.2, C8.2, D1.1, J1.3, J2.3, J3.3, J4.3, J5.1, J6.1, R2.2, R4.2, R6.2, R8.2
unnamed: C3.1, J1.2, R1.1, U1.3
unnamed: C4.1, J2.2, R3.1, U2.3
unnamed: C5.1, J3.2, R5.1, U3.3
unnamed: C6.1, J4.2, R7.1, U4.3
unnamed: D1.2, R9.2
unnamed: R1.2, R2.1, U1.1
unnamed: R3.2, R4.1, U2.1
unnamed: R5.2, R6.1, U3.1
unnamed: R7.2, R8.1, U4.1

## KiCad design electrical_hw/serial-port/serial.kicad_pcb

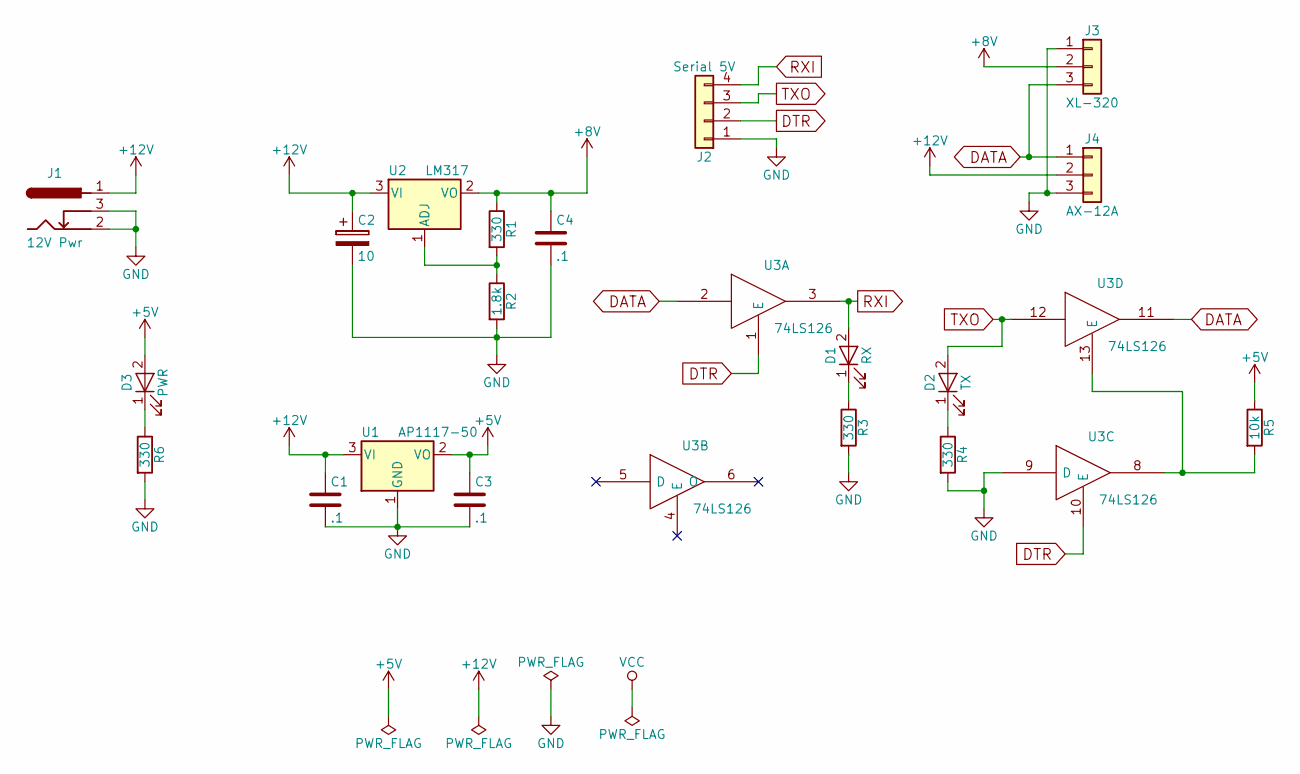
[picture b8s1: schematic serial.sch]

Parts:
C1, C3, C4: .1; C_1206_HandSoldering
C2: 10; CP_Radial_D6.3mm_P2.50mm
D1: RX; LED_1206_HandSoldering
D2: TX; LED_1206_HandSoldering
D3: PWR; LED_1206_HandSoldering
J1: 12V Pwr; BARREL_JACK
J2: Serial 5V; Pin_Header_Straight_1x04_Pitch2.54mm
J3: XL-320; Molex_MicroLatch-53253-0370_03x2.00mm_Straight
J4: AX-12A; Molex_SPOX-5267_22-03-5035_03x2.54mm_Straight
R1, R3, R4, R6: 330; R_1206_HandSoldering
R2: 1.8k; R_1206_HandSoldering
R5: 10k; R_1206_HandSoldering
U1: AP1117-50; SOT-223-3Lead_TabPin2
U2: LM317; TO-220-3_Horizontal
U3: 74LS126; SOIC-14_3.9x8.7mm_Pitch1.27mm

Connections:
+5V: C3.1, D3.2 (A), R5.1, U1.2 (VO)
+8V: C4.1, J3.2, R1.1, U2.2 (VO)
+12V: C1.1, C2.1, J1.1, J4.2, U1.3 (VI), U2.3 (VI)
DATA: J3.3, J4.1, U3.2, U3.11
DTR: J2.2, U3.1 (E), U3.10 (E)
GND: C1.2, C2.2, C3.2, C4.2, J1.2, J1.3, J2.1, J3.1, J4.3, R2.2, R3.2, R4.2, R6.2, U1.1 (GND), U3.7 (GND), U3.9 (D)
unnamed: D1.1 (K), R3.1
unnamed: D2.1 (K), R4.1
unnamed: D3.1 (K), R6.1
unnamed: R1.2, R2.1, U2.1 (ADJ)
unnamed: R5.2, U3.8, U3.13 (E)
RXI: D1.2 (A), J2.4, U3.3
TXO: D2.2 (A), J2.3, U3.12
VCC: U3.14 (VCC)

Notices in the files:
ax12/electrical/power-v2/robot.kicad_pcb:
Walchko (c) 2018
ax12/electrical/rpi/robot.kicad_pcb:
V2 (c) 2018
